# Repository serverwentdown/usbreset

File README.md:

# usbreset

A little dongle-like thing to hard reset USB devices

## KiCad 3D View

## Partially Populated Board

(Note the swapped USB D+/D- wires, those were fixed)

<!-- vim: set conceallevel=2 et ts=2 sw=2: -->

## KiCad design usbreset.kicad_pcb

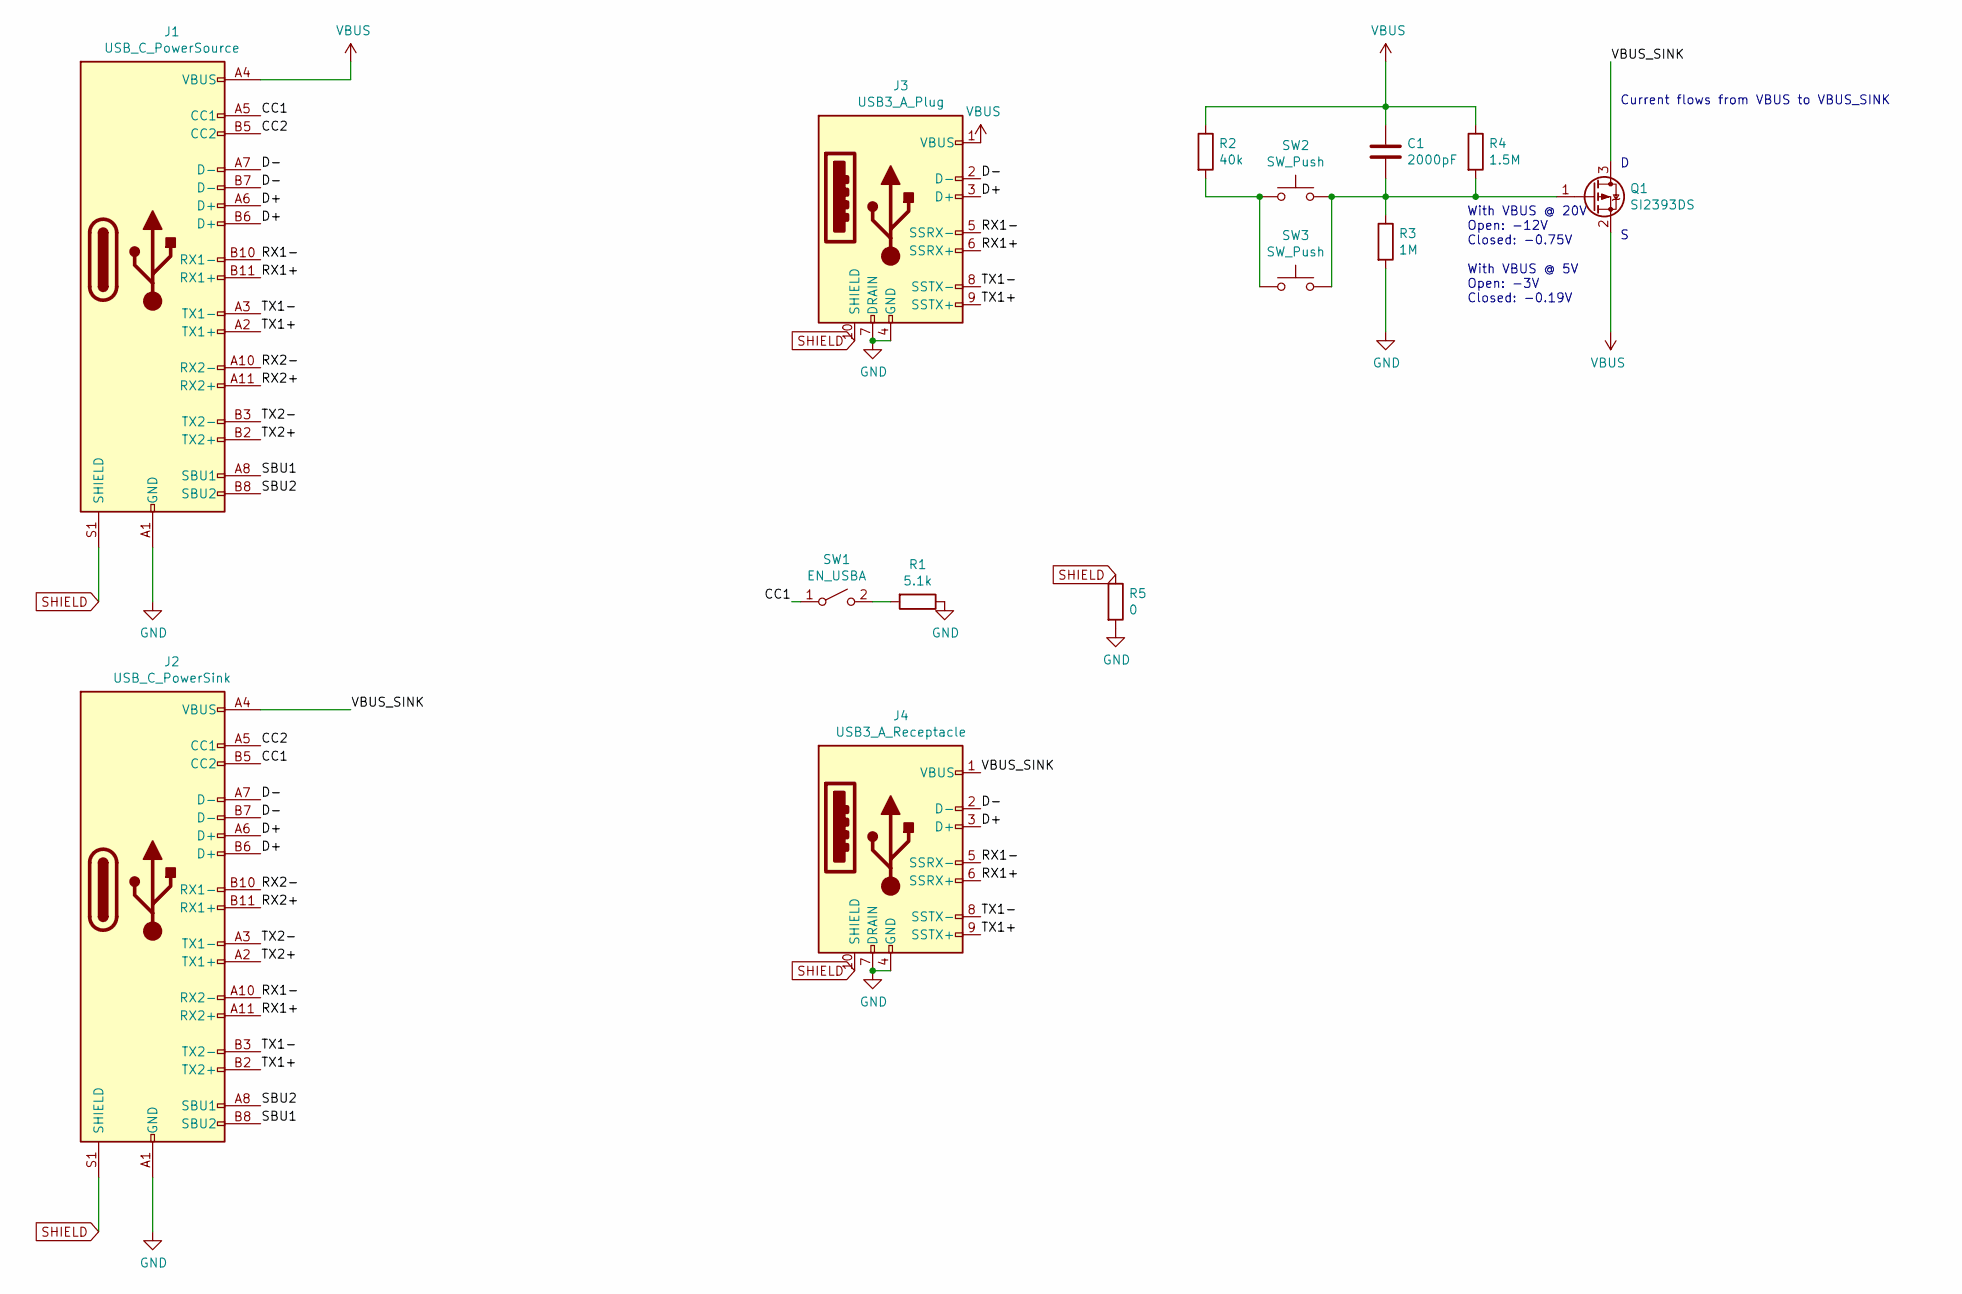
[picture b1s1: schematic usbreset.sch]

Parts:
C1: 2000pF; C_0603_1608Metric
J1: USB_C_PowerSource; USB_C_Receptacle_Amphenol_10137065
J2: USB_C_PowerSink; USB_C_Receptacle_Amphenol_10137065
J3: USB3_A_Plug; USB_A_Plug_Amphenol_GSB3164x1CEU
J4: USB3_A_Receptacle; USB_A_Receptacle_Amphenol_10117835
Q1: SI2393DS; SOT-23
R1: 5.1k; R_0603_1608Metric_Pad1.05x0.95mm_HandSolder
R2: 40k; R_0603_1608Metric_Pad1.05x0.95mm_HandSolder
R3: 1M; R_0603_1608Metric_Pad1.05x0.95mm_HandSolder
R4: 1.5M; R_0603_1608Metric_Pad1.05x0.95mm_HandSolder
R5: 0; R_0603_1608Metric_Pad1.05x0.95mm_HandSolder
SW1: EN_USBA; SW_SPDT_MSS3-V-T_R
SW2: SW_Push; SW_Push_1P1T_NO_CK_KSC7xxJ
SW3: SW_Push; PinHeader_1x02_P2.54mm_Vertical

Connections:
/CC1: J1.A5 (CC1), J2.B5 (CC2), SW1.1 (A)
/CC2: J1.B5 (CC2), J2.A5 (CC1)
/D+: J1.A6 (D+), J1.B6 (D+), J2.A6 (D+), J2.B6 (D+), J3.3 (D+), J4.3 (D+)
/D-: J1.A7 (D-), J1.B7 (D-), J2.A7 (D-), J2.B7 (D-), J3.2 (D-), J4.2 (D-)
/RX1+: J1.B11 (RX1+), J2.A11 (RX2+), J3.6 (SSRX+), J4.6 (SSRX+)
/RX1-: J1.B10 (RX1-), J2.A10 (RX2-), J3.5 (SSRX-), J4.5 (SSRX-)
/RX2+: J1.A11 (RX2+), J2.B11 (RX1+)
/RX2-: J1.A10 (RX2-), J2.B10 (RX1-)
/SBU1: J1.A8 (SBU1), J2.B8 (SBU2)
/SBU2: J1.B8 (SBU2), J2.A8 (SBU1)
/TX1+: J1.A2 (TX1+), J2.B2 (TX2+), J3.9 (SSTX+), J4.9 (SSTX+)
/TX1-: J1.A3 (TX1-), J2.B3 (TX2-), J3.8 (SSTX-), J4.8 (SSTX-)
/TX2+: J1.B2 (TX2+), J2.A2 (TX1+)
/TX2-: J1.B3 (TX2-), J2.A3 (TX1-)
/VBUS_SINK: J2.A4 (VBUS), J2.A9 (VBUS), J2.B4 (VBUS), J2.B9 (VBUS), J4.1 (VBUS), Q1.3 (D)
GND: J1.A1 (GND), J1.A12 (GND), J1.B1 (GND), J1.B12 (GND), J2.A1 (GND), J2.A12 (GND), J2.B1 (GND), J2.B12 (GND), J3.4 (GND), J3.7 (DRAIN), J4.4 (GND), J4.7 (DRAIN), R1.1, R3.2, R5.2
unnamed: C1.2, Q1.1 (G), R3.1, R4.2, SW2.2, SW3.2
unnamed: R1.2, SW1.2 (B)
unnamed: R2.2, SW2.1, SW3.1
SHIELD: J1.S1 (SHIELD), J2.S1 (SHIELD), J3.10 (SHIELD), J4.10 (SHIELD), R5.1
VBUS: C1.1, J1.A4 (VBUS), J1.A9 (VBUS), J1.B4 (VBUS), J1.B9 (VBUS), J3.1 (VBUS), Q1.2 (S), R2.1, R4.1

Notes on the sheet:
Current flows from VBUS to VBUS_SINK
With VBUS @ 20V Open: -12V Closed: -0.75V With VBUS @ 5V Open: -3V Closed: -0.19V

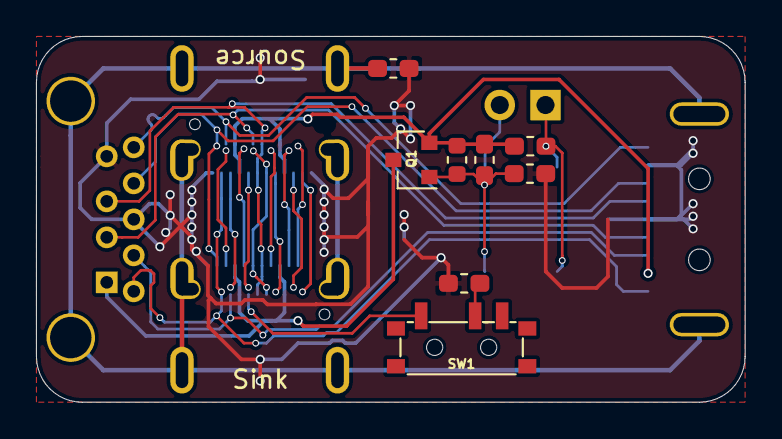
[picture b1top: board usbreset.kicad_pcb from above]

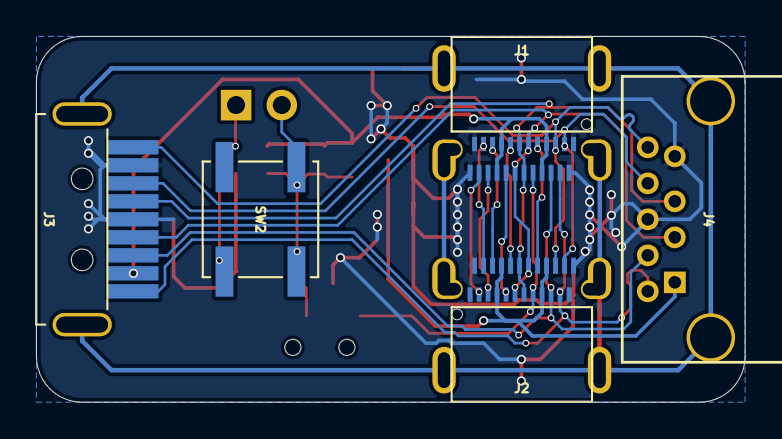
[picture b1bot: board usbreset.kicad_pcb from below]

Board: 2 copper layers, 39.4 x 20.3 mm, 14 parts (6 on the bottom side), 21 nets.

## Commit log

2020-12-13 Initial custom footprints
2020-12-13 Move components to submodule
2020-12-13 Use library in schematic
2020-12-13 Add license
2020-12-13 Update library
2020-12-13 Initial PCB layout
2020-12-13 More tweaks
2020-12-19 Route most connections
2020-12-19 Finish 1st routing pass, add 3D preview
2021-01-10 Improve GND routing
2021-07-02 Add physical soldered prototype
